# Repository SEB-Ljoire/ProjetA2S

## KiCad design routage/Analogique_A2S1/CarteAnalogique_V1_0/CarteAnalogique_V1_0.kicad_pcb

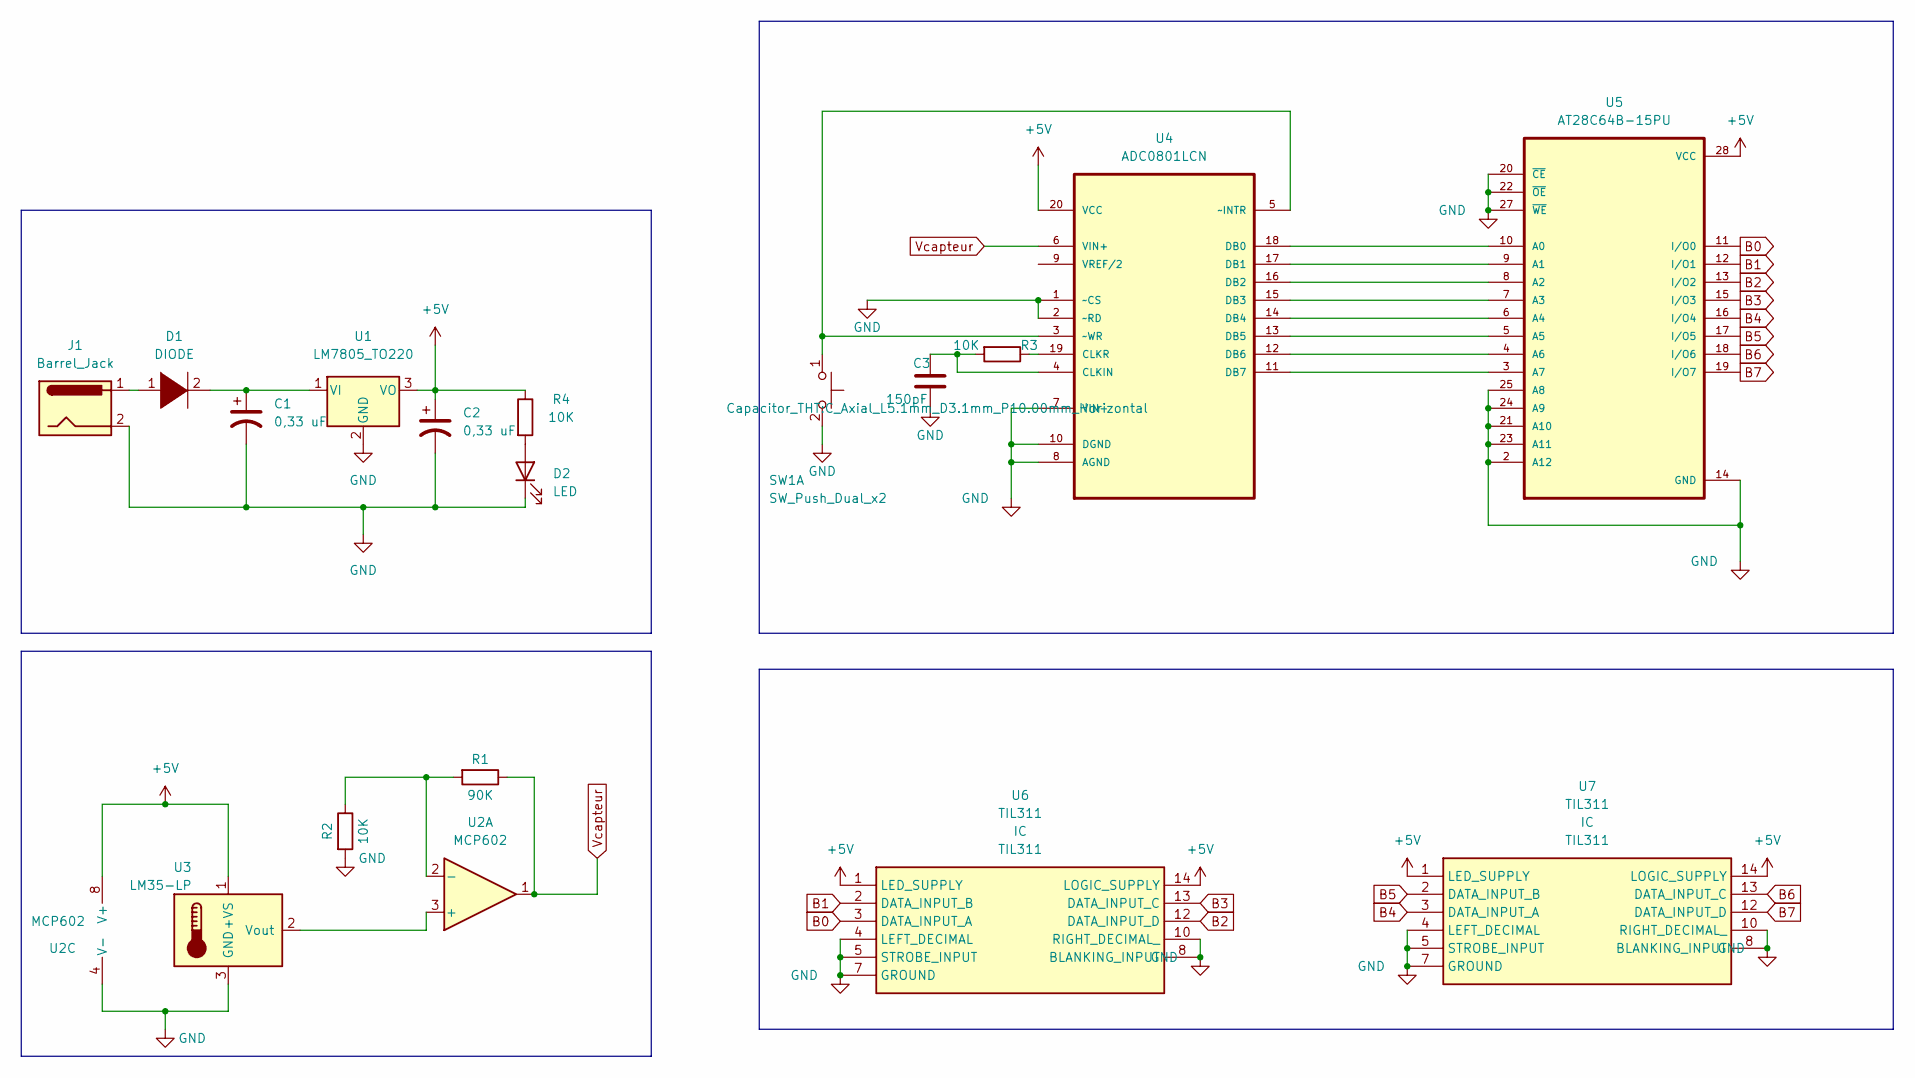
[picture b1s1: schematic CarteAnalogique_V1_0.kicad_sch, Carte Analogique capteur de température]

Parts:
C1: 0,33 uF; CP_Radial_D7.5mm_P2.50mm
C2: 0,33 uF; CP_Radial_D8.0mm_P3.80mm
C3: 150pF; C_Axial_L5.1mm_D3.1mm_P10.00mm_Horizontal
D1: DIODE; D_A-405_P12.70mm_Horizontal
D2: LED; LED_D8.0mm
J1: Barrel_Jack; BarrelJack_CUI_PJ-063AH_Horizontal
R1: 90K; R_Axial_DIN0411_L9.9mm_D3.6mm_P7.62mm_Vertical
R2, R3, R4: 10K; R_Axial_DIN0411_L9.9mm_D3.6mm_P7.62mm_Vertical
SW1: SW_Push_Dual_x2; SW_PUSH_6mm_H13mm
U1: LM7805_TO220; TO-220-3_Vertical
U2: MCP602; DIP-8_W10.16mm
U3: LM35-LP; TO-92
U4: ADC0801LCN; DIP254P762X508-20; MPN ADC0801LCN
U5: AT28C64B-15PU; EEPROM; PARTREV B
U6, U7: TIL311; Mouser Part Number N/A

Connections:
+5V: C2.1, R4.1, U1.3 (VO), U2.8 (V+), U3.1 (+VS), U4.20 (VCC), U5.28 (VCC), U6.1 (LED_SUPPLY), U6.14 (LOGIC_SUPPLY), U7.1 (LED_SUPPLY), U7.14 (LOGIC_SUPPLY)
B0: U5.11 (I/O0), U6.3 (DATA_INPUT_A)
B1: U5.12 (I/O1), U6.2 (DATA_INPUT_B)
B2: U5.13 (I/O2), U6.12 (DATA_INPUT_D)
B3: U5.15 (I/O3), U6.13 (DATA_INPUT_C)
B4: U5.16 (I/O4), U7.3 (DATA_INPUT_A)
B5: U5.17 (I/O5), U7.2 (DATA_INPUT_B)
B6: U5.18 (I/O6), U7.13 (DATA_INPUT_C)
B7: U5.19 (I/O7), U7.12 (DATA_INPUT_D)
GND: C1.2, C2.2, C3.2, D2.1 (K), J1.2, R2.2, SW1.2 (D), U1.2 (GND), U2.4 (V-), U3.3 (GND), U4.1 (~CS), U4.2 (~RD), U4.7 (VIN-), U4.8 (AGND), U4.10 (DGND), U5.2 (A12), U5.14 (GND), U5.20 (~CE), U5.21 (A10), U5.22 (~OE), U5.23 (A11), U5.24 (A9), U5.25 (A8), U5.27 (~WE), U6.4 (LEFT_DECIMAL), U6.5 (STROBE_INPUT), U6.7 (GROUND), U6.8 (BLANKING_INPUT), U6.10 (RIGHT_DECIMAL_), U7.4 (LEFT_DECIMAL), U7.5 (STROBE_INPUT), U7.7 (GROUND), U7.8 (BLANKING_INPUT), U7.10 (RIGHT_DECIMAL_)
unnamed: C1.1, D1.2 (A), U1.1 (VI)
unnamed: D2.2 (A), R4.2
unnamed: D1.1 (K), J1.1
unnamed: R1.2, R2.1, U2.2 (-)
unnamed: U2.3 (+), U3.2 (Vout)
unnamed: SW1.1 (C), U4.3 (~WR), U4.5 (~INTR)
unnamed: C3.1, R3.2, U4.4 (CLKIN)
unnamed: U4.11 (DB7), U5.3 (A7)
unnamed: U4.12 (DB6), U5.4 (A6)
unnamed: U4.13 (DB5), U5.5 (A5)
unnamed: U4.14 (DB4), U5.6 (A4)
unnamed: U4.15 (DB3), U5.7 (A3)
unnamed: U4.16 (DB2), U5.8 (A2)
unnamed: U4.17 (DB1), U5.9 (A1)
unnamed: U4.18 (DB0), U5.10 (A0)
unnamed: R3.1, U4.19 (CLKR)
Vcapteur: R1.1, U2.1, U4.6 (VIN+)

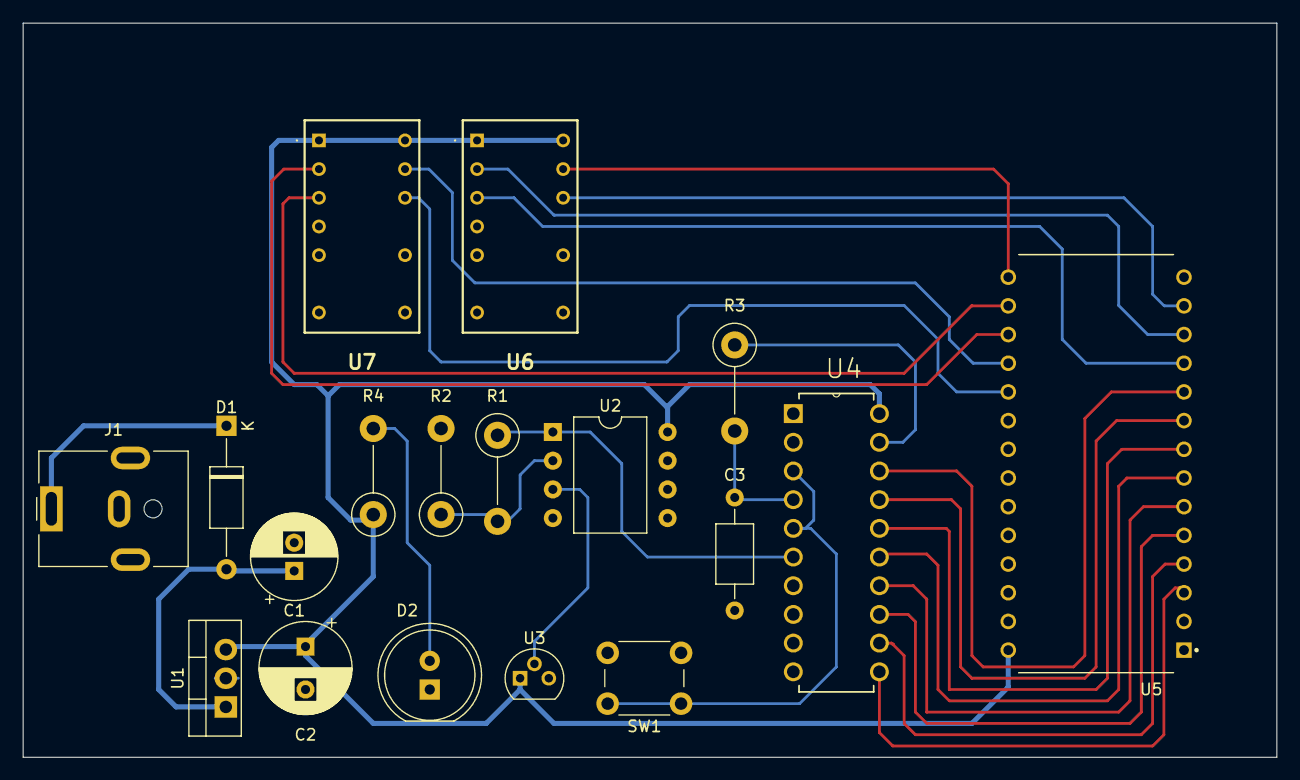
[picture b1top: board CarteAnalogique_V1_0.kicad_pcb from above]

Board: 2 copper layers, 111.0 x 65.0 mm, 18 parts (0 on the bottom side), 27 nets.

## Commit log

2023-11-10 ajout du fichier de CR
2023-12-06 Fichier de validation Capture 5-12V+Sortie capteur
2023-12-12 Rangement des repertoire
    OU RANGER
    Documentation : datasheet, rapport d'essais,tout lien documentaire
    Photo mesure : photo des mesures effectué (screen oscillo,analyseur,photo multi..)
    programme_EEPROM : les programmes de la mémoire avec Versionnement (Version n+1)
    Routage : routage des cartes
    Simulation : Simulation sous LTSPICE ou Proteus
2023-12-12 Ajout de 2 script pour commit simplement
2023-12-12 Ajout d'un choix de branche pour éviter les git conflict
2023-12-12 Début routage
2023-12-16 Creation du routage
2023-12-16 Rangement du répertoire et création du fichier partagé Rapport.docx
2023-12-18 Création du rapport et rangement
2024-03-06 ajout de gitignore
2024-03-06 Rapport et soutenance A1
2024-03-06 routage du projet Analogique premier semestre fermeture de la branche et merge
2024-03-07 Ajout de signal carré et arborescence projet ASM
2024-03-07 Projet kicad microC
2024-03-07 Ajout du projet CAN simulation fonctionnelle
2024-03-07 modification du gitignore pour ajouter les fichier kicad
2024-03-07 Modification du routage ajout de la regulation changement uC et integration Potar pour test CAN
2024-03-07 Modification du port de Sortie en PortB
2024-03-07 Ajout de la partie régulation et condos sur le quartz
2024-03-07 modification du projet et creation du signal Carre prochain commit modif du CAN pour selectionner Vref = Vdd
2024-03-07 Modification du code ASM
2024-03-07 Modification du schema ajout de plusieurs feuille pour schematiser le projet dans ces différentes phase
2024-03-08 Modifcation boucle de retour pour conversion infini et passage de toute les valeurs en binaire a cause des incomprehension en hexa
2024-03-10 modification du projet apres appel kim probleme daffichage sur PORTC
2024-03-11 Creation dune lib pour le decoder LCD et creation d un schema pour la partie 4
2024-03-14 ajout du PDF de cablage next step modif du code signal carre sur pin 2
2024-03-18 ajout du fichier Programme Final
2024-03-18 Modification condo
2024-03-21 modification dans le programmFinal des pin de sortie B
